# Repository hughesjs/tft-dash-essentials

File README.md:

# TFT Dash

A motorcycle dashboard replacement system. An Arduino-based interface board reads sensor signals from the bike — speed, RPM, coolant temperature, fuel level, battery voltage, indicators, and more — and streams data over USB serial to a Raspberry Pi, which renders a real-time graphical dashboard using SDL3.

## System Architecture

```
Phone App (BLE) ──> Arduino Firmware ──> USB Serial ──> Raspberry Pi Display
                    (ATMega32u4)          115200 bps     (SDL3, 1024x600)
                                                               |
                                                    TPMS Sensors (USB Serial)
```

The firmware outputs comma-delimited messages at 115200 bps. The display application deserialises these into dashboard state and renders at 60 fps. A separate TPMS receiver provides tyre pressure data via a second serial connection.

## Display Software Architecture

```
main.c (init, event loop, rendering)
  ├── draw.h          shared rendering state and drawing primitives (in progress)
  ├── dashboard_anims.h/c   animation instances and data tables
  │   └── animation.h/c     generic data-driven animation engine
  ├── sensor_feed.h/c       firmware serial data + comms staleness tracking
  ├── tpms_feed.h/c         tyre pressure serial data
  ├── parser.h/c             serial message deserialisation
  ├── assets.h/c             PNG texture management (stb_image)
  └── menu.h/c               menu screen data tables
```

Pure C23 codebase. Three threads: main (render + animation ticking), sensor feed (firmware serial), and TPMS feed (tyre pressure serial). 62 tests across 6 suites.

## Repository Structure

| Directory | Description |
|---|---|
| `display/` | Display application (C23/SDL3) for Raspberry Pi |
| `firmware/` | Arduino firmware for the sensor interface board (ATMega32u4) |
| `hardware/` | EAGLE schematic/board files for Gen4 PCB + 3D-printable enclosure STLs |
| `simulator/` | .NET/Avalonia desktop simulator for development without hardware |
| `buildroot-tftdash/` | Buildroot external tree for building the Pi SD card image |
| `docs/` | Protocol specs, signal reverse engineering notes, update system design |

## Quick Start

```bash
# Build the display application (requires Zig 0.15+)
make display

# Run all tests
make test

# Build the firmware (requires arduino-cli)
make firmware

# Build the simulator (requires .NET 10)
make simulator

# Full SD card image (firmware + display cross-compile + Buildroot)
make

# See all targets
make help
```

### Bike Model Selection

Uncomment one define at the top of `firmware/firmware.ino`:

- `#define BIKE_FZS1000` — Yamaha FZS1000 Fazer
- `#define BIKE_FZS600` — Yamaha FZS600 Fazer

This controls gear ratios, primary drive ratio, wheel diameter, and RPM calibration.

## Features

- Real-time speed, RPM, coolant temperature, battery voltage, and fuel level
- Gear position indicator (calculated from sprocket ratios)
- Turn indicator, high beam, neutral, and oil warning lights
- TPMS (tyre pressure monitoring) with two hardware variants
- Navigation overlay with turn-by-turn directions
- 9 colour themes with automatic day/night switching
- On-screen menu system for configuration
- NO COMMS warning when serial data goes stale
- Data-driven animation system (startup sequence, RPM effects, transitions)
- A/B rootfs update system for atomic SD card updates

## Documentation

See `docs/` for detailed documentation:

- **`SERIAL-PROTOCOL.md`** — Complete serial protocol specification
- **`signal-reverse-engineering.md`** — Electrical signal details and calibration constants
- **`ab-update-plan.md`** — A/B rootfs update system design
- **`ota-update-plan.md`** — Over-the-air WiFi update architecture (planned)

## Licence

2018-2025 TFTDashProject / Danny Draper.

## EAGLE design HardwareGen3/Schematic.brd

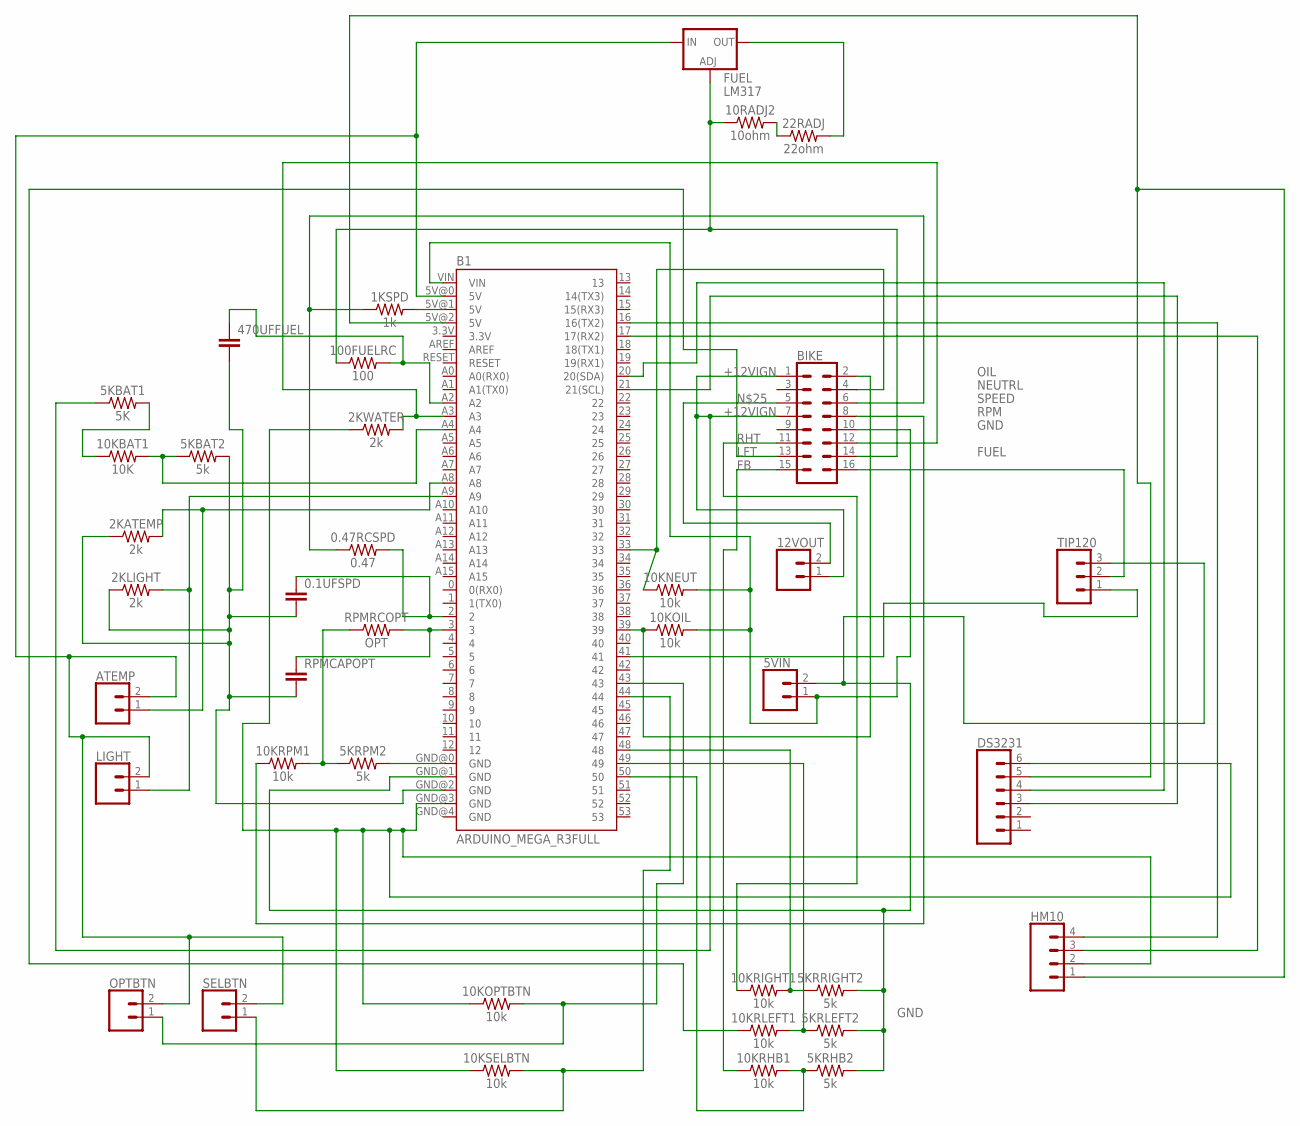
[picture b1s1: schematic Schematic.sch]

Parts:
0.1UFSPD, 470UFFUEL: C2,5-3; C2.5-3
0.47RCSPD: 0.47; AXIAL-0.3
1KSPD: 1k; AXIAL-0.3
2KATEMP, 2KLIGHT, 2KWATER: 2k; AXIAL-0.3
5KBAT1: 5K; AXIAL-0.3
5KBAT2, 5KRHB2, 5KRLEFT2, 5KRPM2, 5KRRIGHT2: 5k; AXIAL-0.3
5VIN, 12VOUT: CONN_02PTH4; 1X02_XTRA_BIG
10KBAT1: 10K; AXIAL-0.3
10KNEUT, 10KOIL, 10KOPTBTN, 10KRHB1, 10KRIGHT1, 10KRLEFT1, 10KRPM1, 10KSELBTN: 10k; AXIAL-0.3
10RADJ2: 10ohm; AXIAL-0.3
22RADJ: 22ohm; AXIAL-0.3
100FUELRC: 100; AXIAL-0.3
ATEMP: CONN_02; 1X02
B1: ARDUINO_MEGA_R3FULL; ARDUINO_MEGA
BIKE: CONN_08X2; 2X8
DS3231: CONN_06SILK_FEMALE_PTH; 1X06
FUEL: LM317; TO220-ADJ
HM10: CONN_04; 1X04
LIGHT: CONN_02; 1X02
OPTBTN: CONN_02; 1X02
RPMCAPOPT: C2,5-3; C2.5-3
RPMRCOPT: OPT; AXIAL-0.3
SELBTN: CONN_02; 1X02
TIP120: CONN_03; 1X03

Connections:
+12VIGN: 5KBAT1.P$1 (1), 12VOUT.1, BIKE.1, BIKE.7
FB: 10KRHB1.P$1 (1), BIKE.15
FUEL: 10RADJ2.P$1 (1), 100FUELRC.P$1 (1), BIKE.14, FUEL.ADJ
GND: 5KRHB2.P$2 (2), 5KRLEFT2.P$2 (2), 5KRRIGHT2.P$2 (2), 5VIN.2, B1.GND@1 (GND), TIP120.3
LFT: 10KRLEFT1.P$1 (1), BIKE.13
unnamed: 2KWATER.P$2 (2), B1.A3, BIKE.12
unnamed: 1KSPD.P$2 (2), B1.5V@1 (5V)
unnamed: 5KRPM2.P$2 (2), B1.GND@0 (GND)
unnamed: 5KRPM2.P$1 (1), 10KRPM1.P$2 (2), RPMRCOPT.P$1 (1)
unnamed: 2KWATER.P$1 (1), 10KOPTBTN.P$1 (1), 10KSELBTN.P$1 (1), B1.GND@3 (GND), DS3231.6, HM10.2
unnamed: 5KBAT1.P$2 (2), 10KBAT1.P$1 (1)
unnamed: 22RADJ.P$2 (2), FUEL.OUT
unnamed: 0.1UFSPD.1, 0.47RCSPD.P$2 (2), B1.2
unnamed: ATEMP.2, B1.5V@0 (5V), FUEL.IN, LIGHT.2, OPTBTN.2, SELBTN.2
unnamed: B1.3, RPMCAPOPT.1, RPMRCOPT.P$2 (2)
unnamed: 10RADJ2.P$2 (2), 22RADJ.P$1 (1)
unnamed: 5VIN.1, 10KNEUT.P$2 (2), 10KOIL.P$2 (2), B1.VIN, BIKE.10
unnamed: B1.41, TIP120.1
unnamed: BIKE.16, TIP120.2
unnamed: 5KBAT2.P$1 (1), 10KBAT1.P$2 (2), B1.A4
unnamed: 0.1UFSPD.2, 2KATEMP.P$1 (1), 2KLIGHT.P$1 (1), 5KBAT2.P$2 (2), 470UFFUEL.2, B1.GND@2 (GND), RPMCAPOPT.2
unnamed: 100FUELRC.P$2 (2), 470UFFUEL.1, B1.A2
unnamed: 2KATEMP.P$2 (2), ATEMP.1, B1.A8
unnamed: 2KLIGHT.P$2 (2), B1.A9, LIGHT.1
unnamed: 10KOPTBTN.P$2 (2), B1.43, OPTBTN.1
unnamed: 10KSELBTN.P$2 (2), B1.44, SELBTN.1
unnamed: 5KRRIGHT2.P$1 (1), 10KRIGHT1.P$2 (2), B1.48
unnamed: 5KRLEFT2.P$1 (1), 10KRLEFT1.P$2 (2), B1.49
unnamed: 5KRHB2.P$1 (1), 10KRHB1.P$2 (2), B1.50
unnamed: 12VOUT.2, BIKE.5
unnamed: B1.5V@2 (5V), DS3231.5, HM10.1
unnamed: B1.20 (20(SDA)), DS3231.4
unnamed: B1.21 (21(SCL)), DS3231.3
unnamed: B1.16 (16(TX2)), HM10.4
unnamed: B1.17 (17(RX2)), HM10.3
NEUTRL: 10KNEUT.P$1 (1), B1.33, BIKE.4
OIL: 10KOIL.P$1 (1), B1.39, BIKE.2
RHT: 10KRIGHT1.P$1 (1), BIKE.11
RPM: 10KRPM1.P$1 (1), BIKE.8
SPEED: 0.47RCSPD.P$1 (1), 1KSPD.P$1 (1), BIKE.6

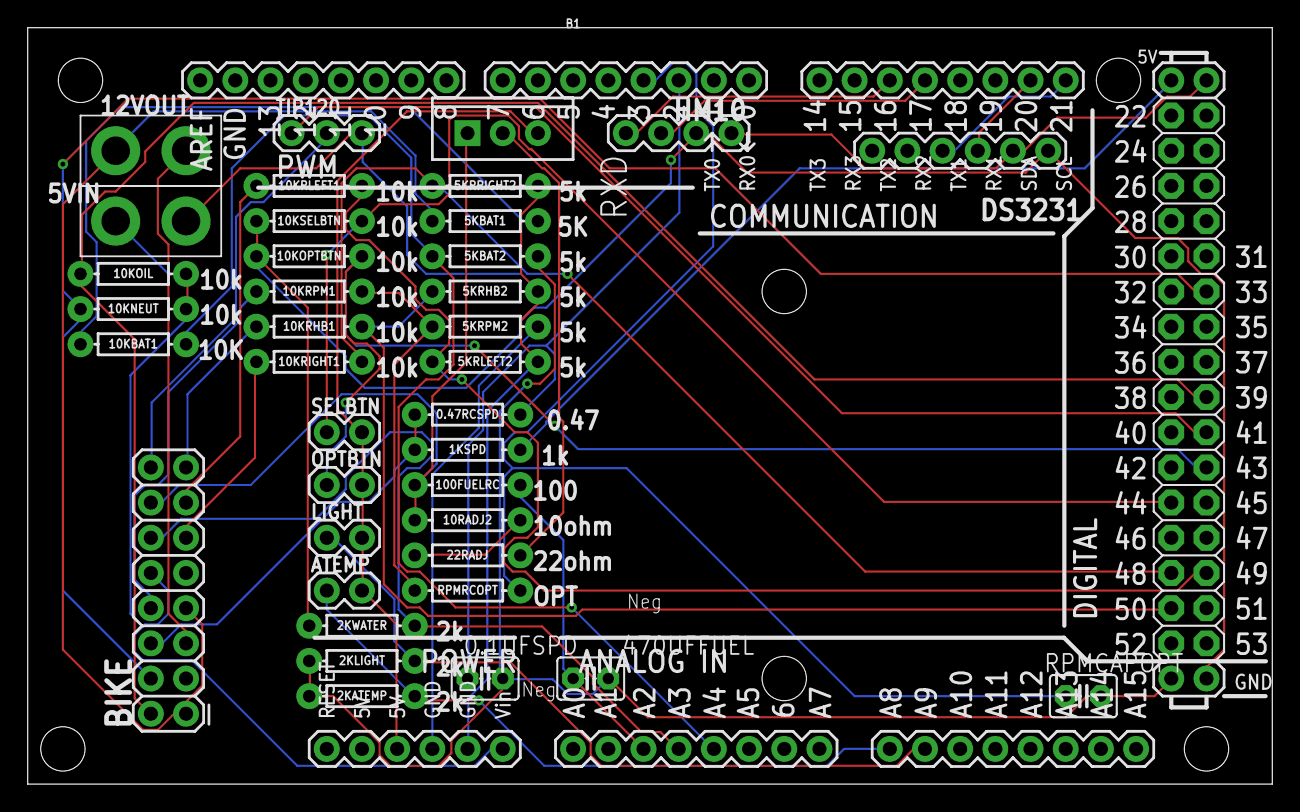
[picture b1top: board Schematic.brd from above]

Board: 2 copper layers, 89.8 x 54.6 mm, 39 parts (0 on the bottom side), 40 nets.

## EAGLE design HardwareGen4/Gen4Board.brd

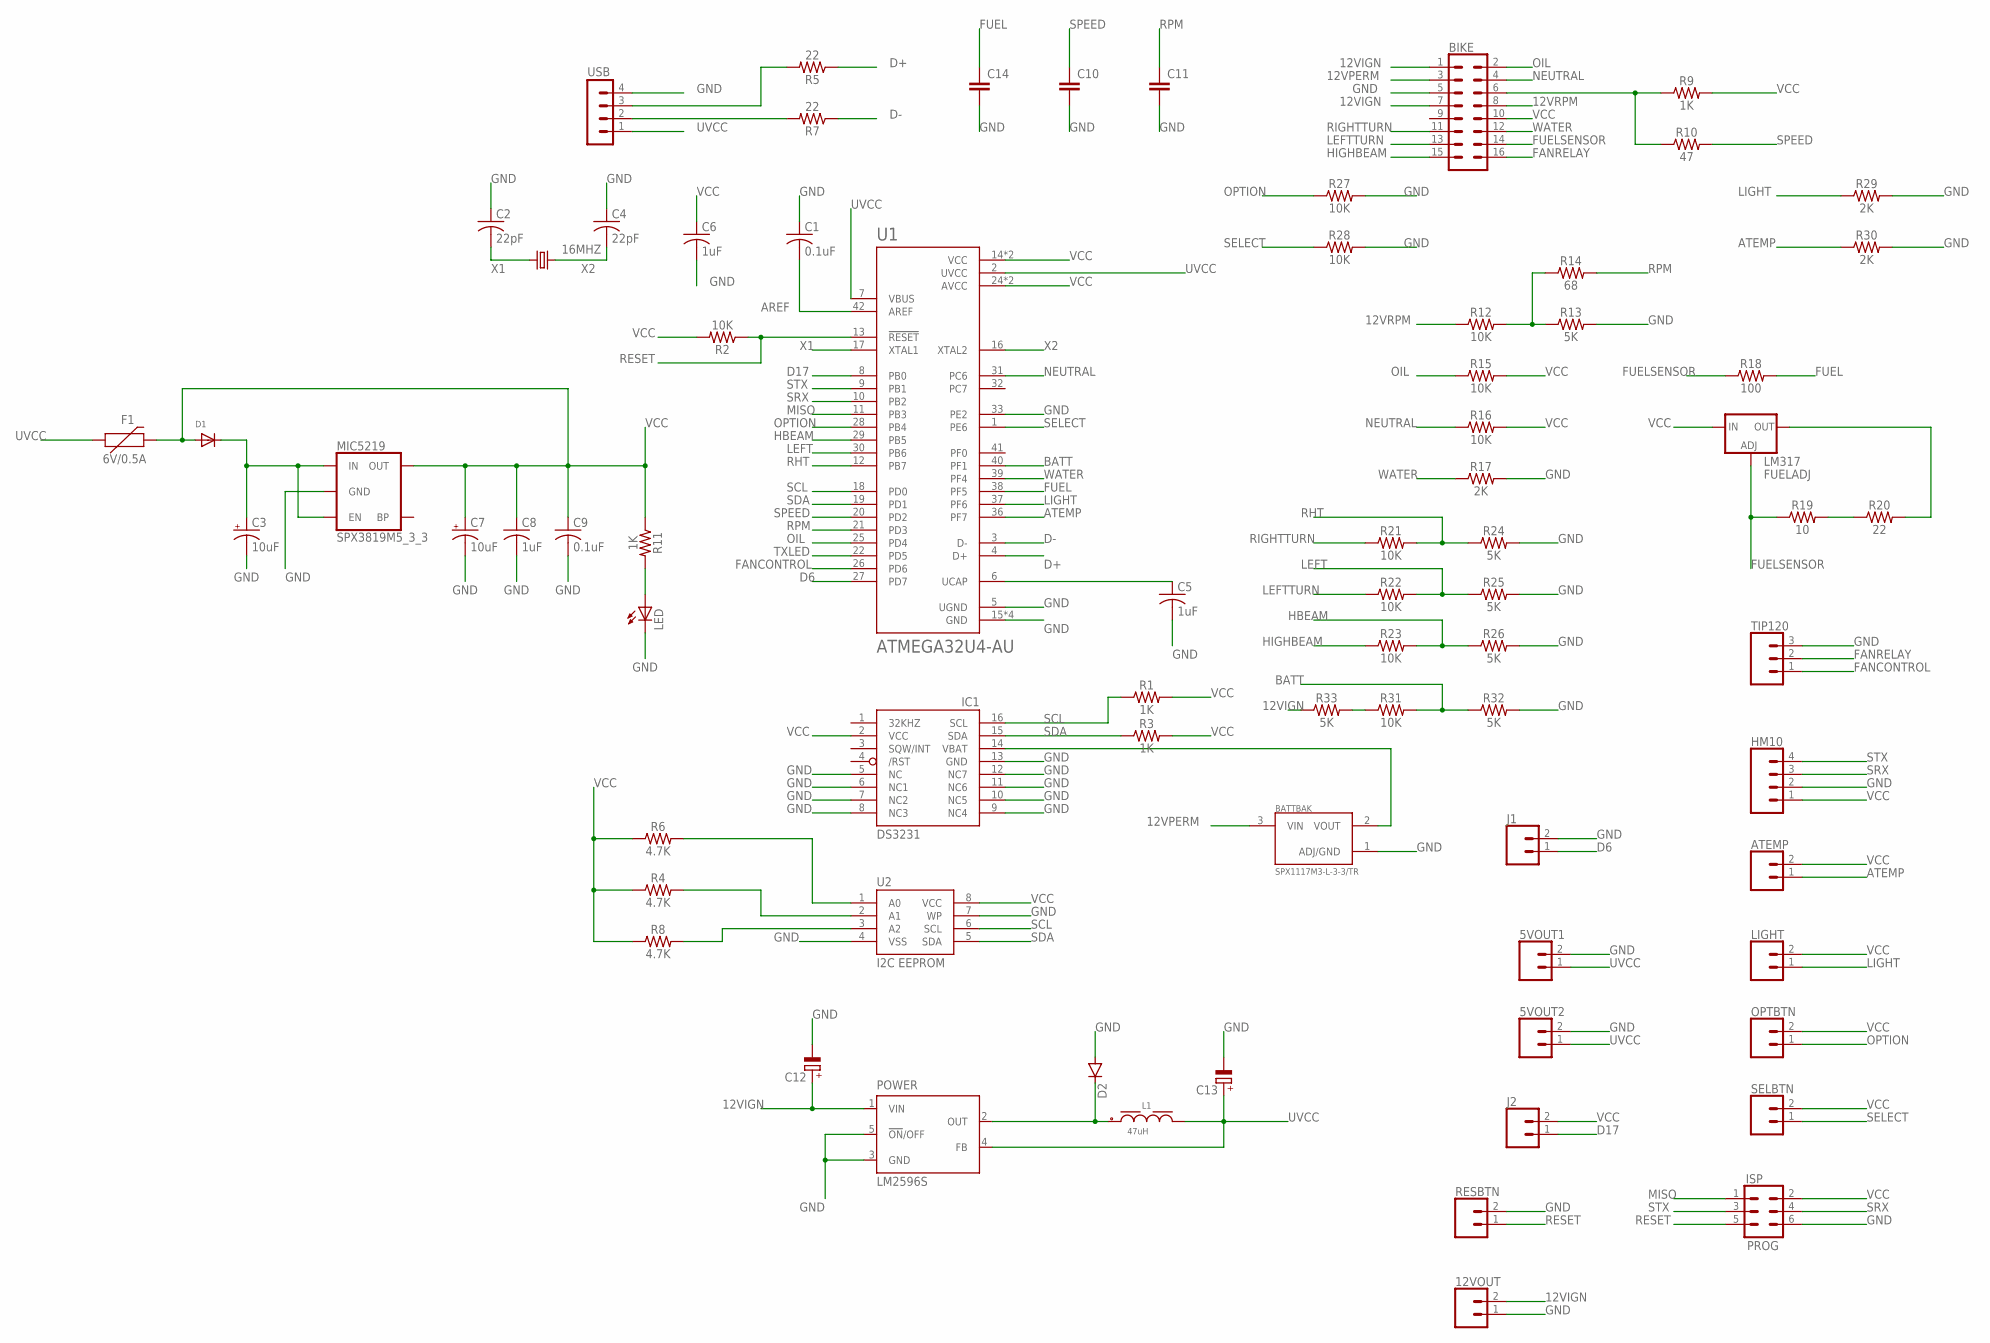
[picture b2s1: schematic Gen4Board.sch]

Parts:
5VOUT1, 5VOUT2, 12VOUT: CONN_02; 1X02
16MHZ: KX-9A; 5.0X3.2_KX-9A
ATEMP: CONN_02; 1X02
BATTBAK: SPX1117M3-L-3-3/TR; SOT230P700X180-3N
BIKE: CONN_08X2; 2X8
C1, C9: 0.1uF; C0603
C2, C4: 22pF; C0603
C3, C7: 10uF; EIA3216
C5, C6, C8: 1uF; C0603
C10, C11, C14: C2,5-3; C2.5-3
C12, C13: CPOL-EUTT5D10; TT5D10
D1: DIODESOD-323F; SOD-323F
D2: DIODE-DO214AC; DO214AC
F1: 6V/0.5A; 1206
HM10: CONN_04; 1X04
IC1: DS3231/SO; SO16W
ISP: PROG; 2X3
J1, J2: CONN_02; 1X02
L1: 47uH; WE-PD_1260
LED: LEDCHIPLED_0603; CHIPLED_0603
LIGHT: CONN_02; 1X02
LM317: FUELADJ; TO220-ADJ
MIC5219: SPX3819M5_3_3; SOT23-5
OPTBTN: CONN_02; 1X02
POWER: LM2596S; TO263-5
R1, R3, R11: 1K; 0603
R2: 10K; 0603
R4, R6, R8: 4.7K; 0603
R5, R7: 22; 0603
R9: 1K; 1206
R10: 47; 1206
R12, R15, R16, R21, R22, R23, R27, R28, R31: 10K; 1206
R13, R24, R25, R26, R32, R33: 5K; 1206
R14: 68; 1206
R17, R29, R30: 2K; 1206
R18: 100; 1206
R19: 10; 1206
R20: 22; 1206
RESBTN: CONN_02; 1X02
SELBTN: CONN_02; 1X02
TIP120: CONN_03; 1X03
U1: ATMEGA32U4-AU; QFP80P1200X1200X120-44N
U2: I2C EEPROM; SO08-EIAJ
USB: MA04-1

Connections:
12VIGN: 12VOUT.2, BIKE.1, BIKE.7, C12.+, POWER.1 (VIN), R33.1
12VPERM: BATTBAK.3 (VIN), BIKE.3
12VRPM: BIKE.8, R12.1
AREF: C1.2, U1.42 (AREF)
ATEMP: ATEMP.1, R30.1, U1.36 (PF7)
BATT: R31.2, R32.1, U1.40 (PF1)
D6: J1.1, U1.27 (PD7)
D17: J2.1, U1.8 (PB0)
D+: R5.1, U1.4 (D+)
D-: R7.1, U1.3 (D-)
FANCONTROL: TIP120.1, U1.26 (PD6)
FANRELAY: BIKE.16, TIP120.2
FUEL: C14.1, R18.2, U1.38 (PF5)
FUELSENSOR: BIKE.14, LM317.ADJ, R18.1, R19.1
GND: 5VOUT1.2, 5VOUT2.2, 12VOUT.1, BATTBAK.1 (ADJ/GND), BIKE.5, C1.1, C2.1, C3.-, C4.1, C5.2, C6.2, C7.-, C8.2, C9.2, C10.2, C11.2, C12.-, C13.-, C14.2, D2.A, HM10.2, IC1.5 (NC), IC1.6 (NC1), IC1.7 (NC2), IC1.8 (NC3), IC1.9 (NC4), IC1.10 (NC5), IC1.11 (NC6), IC1.12 (NC7), IC1.13 (GND), ISP.6, J1.2, LED.C, MIC5219.2 (GND), POWER.3 (GND), POWER.5 (!ON!/OFF), R13.2, R17.2, R24.2, R25.2, R26.2, R27.2, R28.2, R29.2, R30.2, R32.2, RESBTN.2, TIP120.3, U1.5 (UGND), U1.15 (GND), U1.23 (GND), U1.33 (PE2), U1.35 (GND), U1.43 (GND), U2.4 (VSS), U2.7 (WP), USB.4
HBEAM: R23.2, R26.1, U1.29 (PB5)
HIGHBEAM: BIKE.15, R23.1
LEFT: R22.2, R25.1, U1.30 (PB6)
LEFTTURN: BIKE.13, R22.1
LIGHT: LIGHT.1, R29.1, U1.37 (PF6)
MISO: ISP.1, U1.11 (PB3)
unnamed: R7.2, USB.2
unnamed: R5.2, USB.3
unnamed: C5.1, U1.6 (UCAP)
unnamed: LED.A, R11.2
unnamed: C3.+, D1.C, MIC5219.1 (IN), MIC5219.3 (EN)
unnamed: R6.2, U2.1 (A0)
unnamed: R4.2, U2.2 (A1)
unnamed: BATTBAK.2 (VOUT), IC1.14 (VBAT)
unnamed: R8.2, U2.3 (A2)
unnamed: BIKE.6, R9.1, R10.1
unnamed: LM317.OUT, R20.2
unnamed: R12.2, R13.1, R14.1
unnamed: D2.C, L1.1, POWER.2 (OUT)
unnamed: R19.2, R20.1
unnamed: R31.1, R33.2
NEUTRAL: BIKE.4, R16.1, U1.31 (PC6)
OIL: BIKE.2, R15.1, U1.25 (PD4)
OPTION: OPTBTN.1, R27.1, U1.28 (PB4)
RESET: ISP.5, R2.1, RESBTN.1, U1.13 (!RESET)
RHT: R21.2, R24.1, U1.12 (PB7)
RIGHTTURN: BIKE.11, R21.1
RPM: C11.1, R14.2, U1.21 (PD3)
SCL: IC1.16 (SCL), R1.1, U1.18 (PD0), U2.6 (SCL)
SDA: IC1.15 (SDA), R3.1, U1.19 (PD1), U2.5 (SDA)
SELECT: R28.1, SELBTN.1, U1.1 (PE6)
SPEED: C10.1, R10.2, U1.20 (PD2)
SRX: HM10.3, ISP.4, U1.10 (PB2)
STX: HM10.4, ISP.3, U1.9 (PB1)
TXLED: U1.22 (PD5)
UVCC: 5VOUT1.1, 5VOUT2.1, C13.+, F1.1, L1.2, POWER.4 (FB), U1.2 (UVCC), U1.7 (VBUS), USB.1
VCC: ATEMP.2, BIKE.10, C6.1, C7.+, C8.1, C9.1, D1.A, F1.2, HM10.1, IC1.2 (VCC), ISP.2, J2.2, LIGHT.2, LM317.IN, MIC5219.5 (OUT), OPTBTN.2, R1.2, R2.2, R3.2, R4.1, R6.1, R8.1, R9.2, R11.1, R15.2, R16.2, SELBTN.2, U1.14 (VCC), U1.24 (AVCC), U1.34 (VCC), U1.44 (AVCC), U2.8 (VCC)
WATER: BIKE.12, R17.1, U1.39 (PF4)
X1: 16MHZ.1, C2.2, U1.17 (XTAL1)
X2: 16MHZ.3 (2), C4.2, U1.16 (XTAL2)

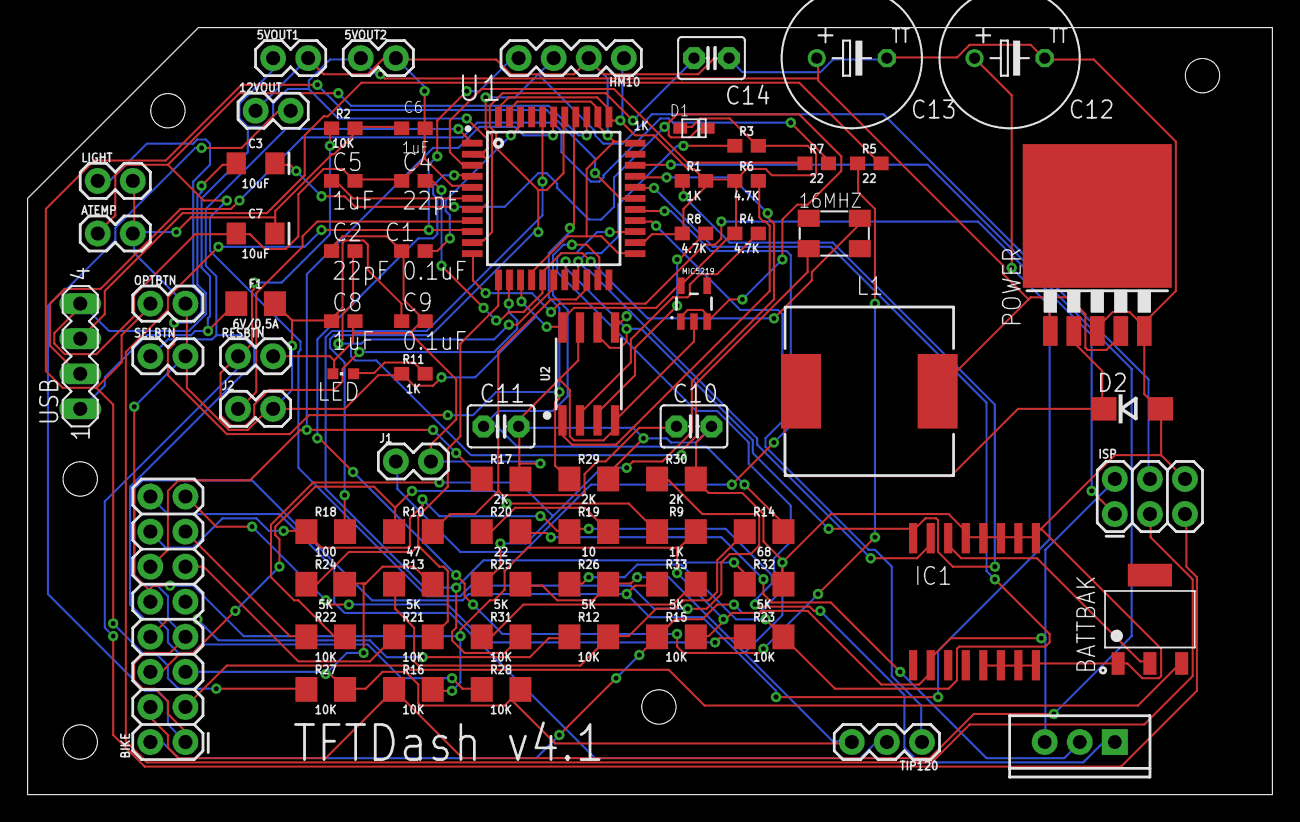
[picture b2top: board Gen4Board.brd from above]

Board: 2 copper layers, 90.2 x 55.5 mm, 75 parts (0 on the bottom side), 54 nets.

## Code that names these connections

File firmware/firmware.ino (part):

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#define FUELPIN     A2
#define COOLANTPIN  A3
#define BATTERYPIN  A4
#define OILLEVELPIN   4 // Goes LOW when oil level is ok 
#define NEUTRALPIN  5 // Goes LOW when in Neutral
#define HIGHBEAMPIN 9 // Goes high when Lit
#define FANPIN   12  // Set high to turn on fan
#define INDICATELEFTPIN  10 // Goes HIGH when lit
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int calcspeedAvg = 0;

// RPM and Floating RPM
int rpm = 0;
unsigned long rpmspeedtime = 0;
unsigned int floatingrpm = 0;
unsigned long rpmAvgpointer = 0;
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  }
  
  if ((micros() - nv_last_rpm_interrupt_time) > 1000000) {
    rpm = 0; 
  }

  floatrpm();
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  }

  if (digitalRead (OILLEVELPIN) == LOW) {
    oillight = 0; // Oil level is ok, it goes LOW when OK and HIGH when not ok.
  } else {
    oillight = 1;
  }

  if (digitalRead (NEUTRALPIN) == LOW) {
    neutrallight = 1; // Goes LOW when in Neutral
  } else {
    neutrallight = 0; // Goes HIGH when in Gear
  }
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
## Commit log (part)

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2020-11-05 Initial commit of TFT Dash Display code - latest as of November 2020
2020-11-06 Remove folder
2020-11-06 Initial add of gfx images for TFT Display
2020-12-12 Updates for Graemes eBay TPMS system.
2021-02-02 Changes to support Navigation
2026-02-06 Add support for tft-dash-simulator pipe
2026-02-06 Update build.sh to detect platform and build correctly
2026-02-07 Reorganise BMPs into assets/themes structure
2026-02-07 Integrate new parser module into main app
2026-02-07 Complete asset reorganization with thumbnails in theme directories
2026-02-07 Refactor to snake_case naming convention throughout codebase
2026-02-12 Add standalone asset manager module with themed texture lookup
    Extracts BMP loading into a reusable assets.h/c module with a two-key
    hash map for (theme, asset_name) lookups. Includes test suite (7 tests)
    and wires into zig build test alongside the parser tests.
2026-02-20 Fix TPMS byte comparisons for ARM char signedness
    On ARM, char is unsigned (0-255), so comparing with negative values
    like -86 and -95 is always false. Use (unsigned char) casts with hex
    constants (0xAA, 0xA1) which work correctly on both signed and
    unsigned char platforms.
2026-02-20 Add cross-compilation support and zig build image step
    - Detect cross-compilation and skip test executables (they link SDL2
    which isn't needed for the Pi image)
    - Add -Dsdl2-include-path and -Dsdl2-lib-path options for pointing at
    Buildroot staging when cross-compiling
    - Add 'zig build image' step that invokes buildroot/build.sh to
    cross-compile and produce an SD card image via Buildroot
2026-02-20 Add Fazer boot splash screen image
    Extracted from the existing tftupdate.zip update package.
2026-02-20 Initial commit: .gitignore
2026-02-20 Reorganised some stuff
2026-02-21 Rename firmware sketch to firmware.ino
2026-02-21 Add firmware build script wrapping arduino-cli
    Provides setup (installs board support + libraries), build, and clean
    subcommands. Used by the top-level Makefile.
2026-02-21 Fix TPMS reconnect loop: add backoff delay and reduce log spam
    Add a 2-second sleep before reconnecting after serial read errors in
    both TPMS poll functions, and only log "NOT connected" on first failure
    instead of every retry.
2026-02-21 Port display application from SDL2 to SDL3
2026-02-21 Statically link SDL3 from source via Zig dependency system
    Replace dynamic linking against system-installed SDL with castholm/SDL
    Zig package that builds SDL3 from source and links statically. This
    eliminates the need for any SDL package in Buildroot and produces a
    self-contained binary.
    - Add castholm/SDL dependency to build.zig.zon
    - Replace linkSystemLibrary("sdl3") with linkLibrary(sdl_lib) in build.zig
2026-02-21 Implement A/B rootfs update mechanism for atomic USB updates
    4-partition SD card layout (boot, rootfs_a, rootfs_b, data) with
    boot-time USB scan and update script that dd's a new rootfs image
    to the standby partition, flips cmdline.txt, and reboots. Verified
    with successful image build producing correct partition table.
2026-03-24 Deduplicate 7 glyph rendering functions into one data-driven renderer
    Replace ~270 lines of near-identical draw_*_string() bodies with a
    single draw_glyph_string() that takes a glyph_font descriptor. Font
    descriptors capture all differences: texture name, sprite atlas coords,
    character set, case sensitivity, spacing, clipping, and per-glyph
    y-offsets. All 86 call sites unchanged via thin wrappers.
2026-03-24 Add navigation controls to simulator
    Symbol dropdown, road/towards text fields, exit number, distance
    (yards/miles), destination distance, and driving-side checkbox.
    Sets InfoMode=3 to activate the nav overlay on the display.
    Includes F5 Navigation preset button.
2026-03-24 Flatten warning badge priority into explicit resolve function
    Replace 4-level nested if/else staircase with a resolve_warning()
    lambda that returns a warning_badge struct. Priority order is now
    a flat list of early-returns: tyre pressure > oil > overheat > fuel.
2026-03-25 Fix nav_state to match actual BLE protocol fields
    The parser's nav_state had generic distance/units string fields that
    didn't match the real protocol (confirmed against Danny's original
    UnpackNavMessage from d1eff26). Updated to match the actual wire
    format: yards (int), miles (double), driving_left (int),
    dest_distance (double). Added TYPE_DOUBLE to parser field system.
2026-03-27 Extract menu data tables into standalone module with tests
    Static const lookup tables for menu screen routing, cursor positions,
    main menu arrow layout, and theme thumbnails. Pure C, no SDL dependency.
    8 tests covering all screen ranges, cursor positions, and edge cases.
    Not yet integrated into testsdl.cpp — module exists alongside for now.
2026-03-27 Add menu state controls and presets to simulator
    Menu-specific properties on DashboardState (sprockets, fan temp, themes,
    light levels, etc.) replace hardcoded values in PipeWriter. New Menu
    section in the UI with controls for all fields, 12 preset buttons for
    each menu screen, and F6-F9 key bindings. PipeWriter now sends both
    live and menu messages when MenuState != 0, matching firmware behaviour.
2026-03-27 Add TPMS feed module with frame decoding and tests
    Opaque tpms_feed struct owns serial connection and background thread.
    Supports both Standard (9600 bps, 0xAA 0xA1) and eBay (19200 bps,
    0x55 0xAA) hardware models. Frame decoding functions exposed for unit
    testing — 9 tests covering both protocols, state flags, sensor ID
    mapping, and edge cases. Not yet integrated into testsdl.cpp.
2026-03-27 Convert display application from C++14 to C23
    Replace lambda with static function, brace-initialised returns with
    compound literals, struct declarations with typedefs. Remove C++ stdlib
    linkage. Rename testsdl.cpp to testsdl.c — all source files now compile
    as C23. No functional changes.
2026-03-27 Rename testsdl.cpp to main.c and binary to dashboard
    Update all references in build.zig, CLAUDE.md, REFACTORING.md, assets
    README, menu module comments, and .gitignore. Rewrite display CLAUDE.md
    to reflect current modular C23 architecture.
2026-03-27 Update buildroot config for testsdl → dashboard rename
    Init script, update script, build script, package recipe, and README
    all updated to reference the new binary name.
2026-03-27 Migrate all assets from BMP to PNG via stb_image
    Replace SDL_LoadBMP() with stb_image PNG loading, added as a Zig
    package dependency (jessechounard/stb_image). All 769 BMP assets
    converted to PNG — total asset size drops from 206 MB to 8.9 MB.
    The colour-key transparency hack for magenta backgrounds is removed;
    PNG's native alpha channel handles transparency properly.
    String references updated across main.c (147), menu.c (95),
2026-03-27 Harden rendering against corrupt serial data
    Replace all sprintf calls with snprintf to prevent buffer overflows
    from unexpectedly large values. Add bounds check on nav symbol lookup
    to prevent out-of-bounds array access.
2026-03-27 Log parse failures in sensor_feed instead of silently dropping frames
    Rejected frames, failed live/menu parses, and failed nav parses now
    log to stderr with the frame length and first 50 bytes of content.
    Aids debugging protocol changes and corrupt serial data.
2026-03-28 Integrate flash animation into dashboard_anims module
    Replace flash_count/flash globals with anim_flash (ANIM_LOOP).
    Warning badges, fuel gauge, and coolant temp flashing now read
    anim_is_reversing(&anim_flash) instead of a manual counter.
    Also adds dashboard_anims.h/c with animation instances, info screen
    transition table, and startup rev counter reveal table. anim_tick_all()
    called once per frame in the main loop.
2026-03-28 Integrate info mode transitions into dashboard_anims module
    Replace 170 lines of repeated if-blocks in animate_info_mode() with
    a table-driven approach. Info screens defined in INFO_SCREENS[] table,
    rendered by a generic render_info_screen() helper. ANIM_PING_PONG
    drives the slide-out/slide-in animation for all mode transitions.
    Also adds Info Mode control (0-3) to the simulator UI.
2026-03-28 Extract rendering code from main.c into focused modules
    main.c drops from 2200 to 332 lines — now just SDL init, event loop,
    and frame dispatch.
    New modules:
    - draw.h/c (432 lines): shared rendering state, sprite atlas tables,
    glyph font system, and all drawing primitives
    - draw_dashboard.h/c (857 lines): startup animation, dashboard
2026-03-28 Clean up main.c — extract init/loop helpers, remove dead code
    main.c drops from 332 to 162 lines. main() is now a clear sequence:
    init_feeds, init_sdl, init_assets, then a loop of tick/refresh/
    handle_events/render/update_warnings.
    Removed: 70-line legacy comment block, unused globals (test_counter,
    reverse, ncount, g_down_arrow_x, g_up_arrow_x), unused functions
    (cycle_digit, file_exists), unused includes (fcntl, termios, errno,
2026-03-28 Add warnings module test suite (18 tests)
    Tests all five warning conditions, priority ordering, engine running
    hysteresis, cancellation, and the dynamic tyre pressure flash texture.
    No SDL dependency — uses a stub for get_num_fuel_bars.
2026-03-28 Move SDL ownership into draw module, main.c is now SDL-free
    draw.c owns SDL init, asset loading, event pumping, frame dispatch,
    and cleanup. main.c has no SDL dependency — just creates feeds,
    calls draw_init/draw_update/draw_frame in a loop.
    main.c drops from 162 to 52 lines (from 2200 at the start of the
    session). The public draw.h interface has three functions:
    draw_init(), draw_update(), draw_frame().
2026-03-28 Eliminate init-time mutable state and simplify main.c to 45 lines
    Replace draw_dashboard_init_rects() with compile-time const
    initialisers for all rects, oil lookup tables, and speedometer
    digit positions. The init function is deleted entirely.
    str_trip_time and str_time initialised at declaration instead of
    from main.c. spd_digit rects replaced with a const position table
    and local rects in draw_speed_digit().
2026-03-28 Merge draw_set_state() into draw_init()
    Sensor state pointers are now passed to draw_init() directly,
    eliminating a separate setup step. One less function in the
    public API.

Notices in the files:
parts and their libraries:
SparkFun-Resistors: Licensing: Creative Commons ShareAlike 4.0 International - https://creativecommons.org/licenses/by-sa/4.0
crystal-geyer_V1_0: Copyright: Geyer-Electronic
Wurth_Power Magnetics_WE-PD: Copyright: Würth Elektronik
